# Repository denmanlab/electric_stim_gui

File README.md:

# STG5 and BRAINSBoard GUI
### This will be a quick guide on how to use all the different tools developed for the BRAINSBoard, STG5 and more!

These are both useful tools used in conjunction with one another to easily allow for multi-channel stimulation of the NeuroNexus A1x16 16-Channel Electrode.
# SECTION 1: HARDWARE
## BRAINSBoard:
### Purpose

The BRAINSBoard is a proprietary custom PCB that is designed to electronically switch between Cathode, Anode, Ground, and Floating states for 16 different electrode channels without physically interacting with the components during experiments. This enables:
- Stimulation at different loci in patterns.
- Grounding of every inactive pin to prevent noise.
- Use with a GUI designed for efficient pin switching during and between experiments.

### Components of the Board

#### Connectors
- $\textbf{\color{yellow}Raspberry Pi/Arduino 2x20 Female Header}$ facilitates connections to control and process data from Arduino/Raspberry Pi. $\textbf{\color{yellow}2x20 90º Male Header}$ allows external connections to unused/useful pins
  - Raspberry Pi can be directly connected on top of the $\textbf{\color{yellow}2x20 Female Header}$. Connection Pinout as follows:

  - An Arduino can be connected to those same pins with the following Pinout (demonstrated with Arduino Pro Mini):

  - Other tools (ie. sensors, actuators, external triggers) can be accessed from the $\textbf{\color{yellow}2x20 90º Male Header}$ with the following Pinout:

- $\textbf{\color{white}NeuroNexus}$ Standard 2x8 Box Connectors with grounding on all top pins to minimize noise. Pinout:

- $\textbf{\color{red}Banana Connectors:}$ Connects to cathode and anode pulses from an Isolated Analog Power Stimulator (preferred STG5) and a Signal Ground that can be connected to the same common ground as the electrode and stimulator.

#### Products Used:

$\textbf{\color{yellow}External Connectors:}$

[2x20 Female Header](https://www.digikey.com/en/products/detail/te-connectivity-amp-connectors/2-215307-0/1149668)

[2x20 90º Male Header](https://www.digikey.com/en/products/detail/oupiin/2011-2X20G00RB/13251482)

$\textbf{\color{white}Connectors to Neuronexus:}$

**Samtec Box Header** from [Digikey](https://www.digikey.com/en/products/detail/samtec-inc/TSS-108-01-G-D/2345166):

$\textbf{\color{red}Connectors to Analog Stimulus Isolator:}$

[Ground Connector](https://www.digikey.com/en/products/detail/cliff-electronic-components-ltd/FCR7350G/17729033)

[Cathode Stimulus Connector](https://www.digikey.com/en/products/detail/pomona-electronics/73099-2/10483465)

[Anode Stimulus Connector](https://www.digikey.com/en/products/detail/pomona-electronics/73099-0/10483460)

### Electronics for Selecting Channels:

The following are used to be able to utilize Arduino Logic and rapidly change the connection between our stimulus signal from the isolated stimulator and the respective electrode channels.

#### $\textbf{\color{#FF69B4}Octal Transparent D-Type Latch}$
- Requires a VCC +5V and ground.
- Output Enable and Latch Enable controls, connected to Arduino/Raspberry Pi, to manage pin outputs.
- Utilizes multiplexing capabilities to reduce connections needed to the microcontronoller and allows for future scalability.
- Latch capabilities ensure channel selection stability until change is required.
- [Texas Instruments Octal Transparent D-Type Latch](https://www.digikey.com/en/products/detail/texas-instruments/CY74FCT373TSOC/1508737)

#### $\textbf{\color{orange}Analog SP3T Switch}$
- Two inputs determine the current path (cathode, anode, ground, or floating).
- Output directed through a connector managing pin outputs.
- Useful digital switch to ensure one of the four output states is set at all times.
- [Texas Instruments Analog SP3T Switch](https://www.digikey.com/en/products/detail/texas-instruments/TS5A3357DCUR/695801)

#### $\textbf{\color{cyan}Solid State Relay}$
- Activated by a control switch, it powers an LED internally, which in turn activates a photosensitive diode to close the circuit.
- Optical Isolation prevents electrical interference from the microcontroller side of the circuit to the Analog Isolator stimulus sent to the respective channels.
- These specific Solid State Relays will be useful in handling high variance in Volatge due to unpredictable resistance in the brain as current stimulus is sent.
- [IXYS 600V 100mA Dual Single Pole Normally Open Relay](https://www.digikey.com/en/products/detail/ixys-integrated-circuits-division/PAA193STR/3077694)

#### $\textbf{\color{green}LEDS}$
- Top LED is a $\text{\color{red}RED LED}$ that is utilized to indicate whether or not the BRAINS Board is receiving power.
- Bottom LED is a $\text{\color{green}GREEN LED}$ that is utilized to indicate whether the Output Enable is activated, determining whether or not outputs are being sent to change channels

# SECTION 2: BRAINS BOARD SPECIFIC SOFTWARE

There are various sets of code designed to interface with the BRAINS Board through either the Arduino or Raspberry Pi.
These are guides on how they are designed as well as a simple measure as to how they may be manipulated for various uses.

## PART 1: Using Serial Communication with Arduino to Map Channels:

The current BRAINS Board API is built around Serial Inputs that are translated into pin activation using the [Brainsboard Serial Program Arduino Code](brainsboard_serial_pgm.ino)

This is also all right now designed to be used alongside an Arduino Micro Pro with the pinout shown above in [this image](images/BB2ProMicro_bb.png), though it can easily be changed to work with any Arduino board and pinout using the #define functions.

The following pins correspond to channels above:
| Electrode Channel |    Arduino Pins     |
|:-----------------:|:-------------------:|
| Channel **1**     | Pin 16 + 1 + 5 + 6  |
| Channel **2**     | Pin 16 + 1 + 7 + 8  |
| Channel **3**     | Pin 16 + 1 + 9 + 10 |
| Channel **4**     | Pin 16 + 1 + 14 + 15|
| Channel **5**     | Pin 16 + 2 + 5 + 6  |
| Channel **6**     | Pin 16 + 2 + 7 + 8  |
| Channel **7**     | Pin 16 + 2 + 9 + 10 |
| Channel **8**     | Pin 16 + 2 + 14 + 15|
| Channel **9**     | Pin 16 + 3 + 5 + 6  |
| Channel **10**    | Pin 16 + 3 + 7 + 8  |
| Channel **11**    | Pin 16 + 3 + 9 + 10 |
| Channel **12**    | Pin 16 + 3 + 14 + 15|
| Channel **13**    | Pin 16 + 4 + 5 + 6  |
| Channel **14**    | Pin 16 + 4 + 7 + 8  |
| Channel **15**    | Pin 16 + 4 + 9 + 10 |
| Channel **16**    | Pin 16 + 4 + 14 + 15|

**The logic is this way because of the following:**

- Our **Output Enable** pin, that is connected to all 4 of the Octal Latches, is connected to **Arduino Pin 16**
- We have 4 **Latch Enable** pins that are used to determine which latch we are controlling
  - **Pin 1** is connected to the first **OCTAL LATCH**, which controls signals sent to the **SP3T** switches that set channel configuration for **Electrode Channels 1-4**
  - **Pin 2** is connected to the second **OCTAL LATCH**, which controls signals sent to the **SP3T** switches that set channel configuration for **Electrode Channels 5-8**
  - **Pin 3** is connected to the third **OCTAL LATCH**, which controls signals sent to the **SP3T** switches that set channel configuration for **Electrode Channels 9-12**
  - **Pin 4** is connected to the fourth **OCTAL LATCH**, which controls signals sent to the **SP3T** switches that set channel configuration for **Electrode Channels 13-16**
- We then have **8 Data Input** pins connected to all of the **Octal Latches**, which will change the state of the digital output of the latches to High or Low dependent on a) if the latch enable for said Octal Latch is on and b) if the Arduino pin connected to each digital input pin is high or low
  - **Pins 5 and 6** control the output to the **SP3T** controlling **Electrode Channels 1, 5, 9, and 13**.
  - **Pins 7 and 8** control the output to the **SP3T** controlling **Electrode Channels 2, 6, 10, and 14**.
  - **Pins 9 and 10** control the output to the **SP3T** controlling **Electrode Channels 3, 7, 11, and 15**.
  - **Pins 14 and 15** control the output to the **SP3T** controlling **Electrode Channels 4, 8, 12, and 16**.

**Important Note:** The **A0 pin** is used as an input of any External Triggers from any other device (ie. a stimulator) for the board to use as an input to switch channels, if required.

The code also has 4 states that any channel can be set to at any given moment: **FLOATING**, **CATHODE**, **ANODE**, and **SIGNAL GROUND**. The board is designed to allow the **OCTAL LATCH** to send 2 outputs to any given **SP3T** correlated to a specific electrode channel, and logic of the switch by the **SP3T** is treated as follows:
| INPUT 1 STATE | INPUT 2 STATE | CHANNEL CONNECTED |
|:-------------:|:-------------:|:-----------------:|
| **LOW**       | **LOW**       | **FLOATING**      |
| **HIGH**      | **LOW**       | **CATHODE**       |
| **LOW**       | **HIGH**      | **ANODE**         |
| **HIGH**      | **HIGH**      | **SIGNAL GROUND** |

**Important Note:** The **SIGNAL GROUND** is connecting any signal connected to the $\textbf{\color{green}Green Banana Connector}$, which should ideally connected to the same **Reference Ground** that you would use for any electrophysiology or stimulation experiment.

### Serial Communication Logic:
**The following is a step-by-step guide for utilizing any serial communication to control the channel outputs at any given time**
1. Ensure you are using 115200 bps as the data rate for for Serial line
2. '[' Begins reading channel Data
3. **'{X1}'** is a *Hexadecimal Number*
    - **To Set Channels 1-10:** X1 corresponds to a numerical value Channel # - 1 (ie. Channel 1 is 0, Channel 2 is 1, ..., Channel 10 is 9)
    - **To Set Channels 11-16:** X1 corresponds to an alphabtical value between A-F (ie. Channel 11 is A, Channel 12 is B, ..., Channel 16 is F)
4. **'{X2}'** is a *Character*
      - **F** for **FLOATING**
      - **C** for **CATHODE**
      - **A** for **ANODE**
      - **G** for **SIGNAL GROUND**
5. **']'** Closes *Reading Channel States* and *"Applies"* the channel states by utilizing logic to change where channels are connected
6. **'x'** Sets a *wait* until the **External Trigger Pin** recieves a signal (and won't continue until that trigger is low to change anything)
7. **'{t}{u}'** Sets a *wait* for a set time
      - **'{t}'** is a *numerical value* that is read and stored until the serial code reads a non-numerical value
      - **'{u}'** is a *character* that is written after the numerical values have been written that determines the units of delay time
        - **s** will set the *time {t}* to seconds
        - **m** will set the *time {t}* to milliseconds
        - **u** will set the *time {t}* to microseconds
8. **'l{c}'** Sets up a *loop* for the inputted channel setups for *{c}* more counts
      - If *{c}* is not set, it will infinitely loop.
9. **Important Note:** It is not necessary to write out every channel, previous channel states are already stored and latched until that specific channel is changed
#### Example Serial Command:
**[0F1F2F3F4F5F6F7F8F9FAFBFCFDFEFFF]200u[0C1A]x[0G1GEAFC]2sl3**
- This will first **set every channel** to **FLOATING**
- It will then **wait 200 microseconds**
- It will then change **Channel 1** to **CATHODE** and **Channel 2** to **ANODE**
- It will then **wait** until it recieves the **External Trigger** at **Pin A0**
- It will then change **Channel 1** and **Channel 2** to **SIGNAL GROUND** and **Channel 15** to **ANODE** and **Channel 16** to **CATHODE**
- It will then **wait 2 seconds**
- It then reads **l3**, so it will **loop** the previous steps **3 more times**

## PART 2: Using the Raspberry Pi to Map Channels Directly

The BRAINS Board was initially designed to directly integrate the various connections on a Raspberry Pi to map pins to channels and work harmoniously as a modular device that can work alongside other tools in an experimental setting. There are both benefits and drawbacks to using this microcontroller over an Arduino, laid out as follows:
### BENEFITS:
1. BRAINS Board easily snaps into a Raspberry Pi, no external connection is needed
2. Any pins not used to directly control the logic of the BRAINS Board can be easily accessed through the side male pins, following the pinout shown above in [this image](images/BB_2_external_pins_Pinout.png)
3. Doesn't rely on Serial Communication to switch pinout, which can reduce latency
4. Allows for communication over WiFi which allows for non-wired control to directly switch channels
**When Using This Microcontroller Is Better:** The ideal use for the Raspberry Pi over an Arduino is when you are just reading an external signal or series of them and want to create a closed loop transition between channels based on multiple complicated inputs feeding directly into the Raspberry Pi, given that those inputs are able to be read by the Linux system and processed that way, **OR** when latency isn't very important but non-wired communication is essential or easier. 
### DRAWBACKS:
1. Raspberry Pi uses CPU for running Debian, can create unwanted latency due to other processes running
2. Latency of WiFi communication relatively high
3. Serial read latency of Raspberry Pi is higher than Arduino Serial read latency
4. Debian (Linux) software won't run various softwares (many stimulator softwares are written specifically for Windows computer)
**When Using This Microcontroller is Not Optimal:** The Arduino controller is better when running integrated software with other devices that need a computer to process the information or program other things at the same time (ie. the STG5 Isolated Analog Stimulator, a MultiChannelSystems product that can only be customizably programmed on a Windows using their .dll Package for Windows) **OR** if latency based on external readings is critical and the processing can't be done on a Raspberry Pi (ie. if there were a developed closed-loop system based on the readings of inserted Neuropixels real-time to manipulate activated channels in a closed-loop system).

With that said, there are only a few changes in terms of the pinout when programming as such, all already established with the [GPIO](GPIO.py) script already set. The connections to the BRAINS Board from GPIO pins on the Raspberry Pi are as follows:

| PIN ON BRAINS BOARD | GPIO PIN ON RASPBERRY PI |
|:-------------------:|:------------------------:|
|**OE PIN**           | 22                       |
|**LE PIN 1**         | 23                       |
|**LE PIN 2**         | 24                       |
|**LE PIN 3**         | 25                       |
|**LE PIN 4**         | 27                       |
|**DIGITAL INPUT 1**  | 5                        |
|**DIGITAL INPUT 2**  | 6                        |
|**DIGITAL INPUT 3**  | 12                       |
|**DIGITAL INPUT 4**  | 13                       |
|**DIGITAL INPUT 5**  | 16                       |
|**DIGITAL INPUT 6**  | 17                       |
|**DIGITAL INPUT 7**  | 19                       |
|**DIGITAL INPUT 8**  | 26                       |

The GPIO code uses these and just takes 16 individual strings as channel_state = [...] with **F** for **FLOATING**, **C** for **CATHODE**, **A** for **ANODE**, and **G** for **SIGNAL GROUND** and the delay can be set using the precise_sleep function. Use general Python functionality to be able to program this any which way.

# SECTION 3: STG5

The stimulator of choice for this project is the [Multi Channel Systems STG5](https://www.multichannelsystems.com/products/stg5-base). This product has all the stimulating capabilities that we require for our electrophysiology experiments, can both recieve external triggers and produce a digital output that can be aligned with an analog stimulus sent, and is most importantly programmable beyond the base software that comes with the STG5. We designed our own custom GUI to perform stimulation experiments for monopolar, bipolar, and multipolar stimulation that can be paired with the BRAINS Board. Lets break down the various features of our GUI:

## FEATURE 1: LOCALHOST WEB GUI:

The GUI is all written in Python, but utilizes the [Holoviz Panel Library](https://panel.holoviz.org/index.html) to setup a locally hosted Web GUI that can run on any device
**IMPORTANT NOTE:** THE GUI MUST BE RUN ON A WINDOWS DEVICE IN ORDER TO CONNECT WITH THE STG5 GUI
**IMPORTANT NOTE 2:** THE MCSUsbNet .dll package must be setup from [here](https://github.com/multichannelsystems/McsUsbNet/tree/086642d15fa1b8b805cdc137db4652151c30f9f5) in order to work. Ensure that the packages and files in the MCSUsbNet folder in this repository have all the required permissions to run, otherwise there will be errors.

**Once everything is setup, run the [STG5 and BRAINS Board Joint GUI](STG5_BRAINSBoard_Joint_GUI.py) Python Script to start up the GUI so that you can manipulate the next features

## FEATURE 2: EVENT SETTINGS:

When you first run the GUI, the *EVENT SETTINGS* tab will be the primary tab opened. You will notice the following:
- First you will have the *Waveform Type Selector* that has three options: **Monophasic**, **Biphasic**, and **Sinusoidal**
- You will have the *Modulation Type Selector* directly underneath it, giving the options of sending a set **Voltage** or **Current** from the STG5
- You then have the *Amplitude Selection* underneath those two Radio Buttons
  - On the left is the *Amplitude Slider* where you can easily set the numeric value for your Amplitude
  - Next to the slider, you get the *Unit Selector*, which gives you the option of setting the units of your waveform. If **Voltage** is selected from your *Modulation Type Selector*, your options are **uV**, **mV** or **V** and if **Current** is selected from your *Modulation Type Selector*, your options are **uA**, **mA**, or **A**.
  - You also have the *Randomize* slider and button, which allows you to choose a range and randomize the amplitude of your waveform when the random button is clicked.
- If **Monophasic** or **Biphasic** is selected:
  - There is a *Pulse Duration Slider* and *Unit Selector Button* for setting the Pulse Duration in microseconds, milliseconds, or seconds
  - If **Biphasic** specifically is selected, there will be text stating whether the waveform is **Cathode Leading**, **Anode Leading**, or **Neither** and it is **IMPORTANT TO NOTE: THE PULSE DURATION IS SET FOR ONE HALF OF THE WAVEFORM, NOT TOTAL PUSLE DURATION**
  - You also get a *Randomizer* pulse duration if needed.
- If **Sinusoidal** is selected:
   - You get a *Wavelength Type Selector* that gives you the option to choose between setting the Period or Frequency of the Waveform, with a *Wavelength Slider* with the same functionality as other sliders with a *Unit Selector* and *Randomizer*
   - There will also be a conversion printed at the bottom with either Frequency or Period, opposite of what is selected in the selector
- There is also a *Number of Events* input, normally set to 1.
   - If set to one, nothing else needs to be done
   - If set >1, there will be an option to set a duration between events using the *duration between events slider* with both *unit selection* and *randomize* functionality.
This is all the settings for one "event", giving basic functionality for setting up a waveform.

## FEATURE 2: TRAIN SETTINGS
This feature is established to allow you to repeat events as individual trains for however many trains are needed for an experiment. The following can be set:
- First and foremost is the *External Trigger checkbox* that allows you to start a train based on an external trigger recieved by the STG5. Functionality of this function is still in the process of being built.
- Next is the *Number of Trains Input* that allows you to set the number of trains in one run
- If more than 1 train in set, you can then use the *Time Between Trains* slider to set the amount of **time between the start of one train to the start of the next train** (ensure this is bigger than the total time of one event) that also has *unit selection* and *randomize* features.

## FEATURE 3: EXTERNAL SIGNAL SETTINGS
This feature allows you to send out an external digital signal from a channel of the STG5 of any specified length at the beginning of every train. This is done using the *External Signal Slider* with *unit selection* and *randomize* functionality.
## $\textbf{\color{white}This work was supported by NIH NINDS project number 1R01NS120850}$

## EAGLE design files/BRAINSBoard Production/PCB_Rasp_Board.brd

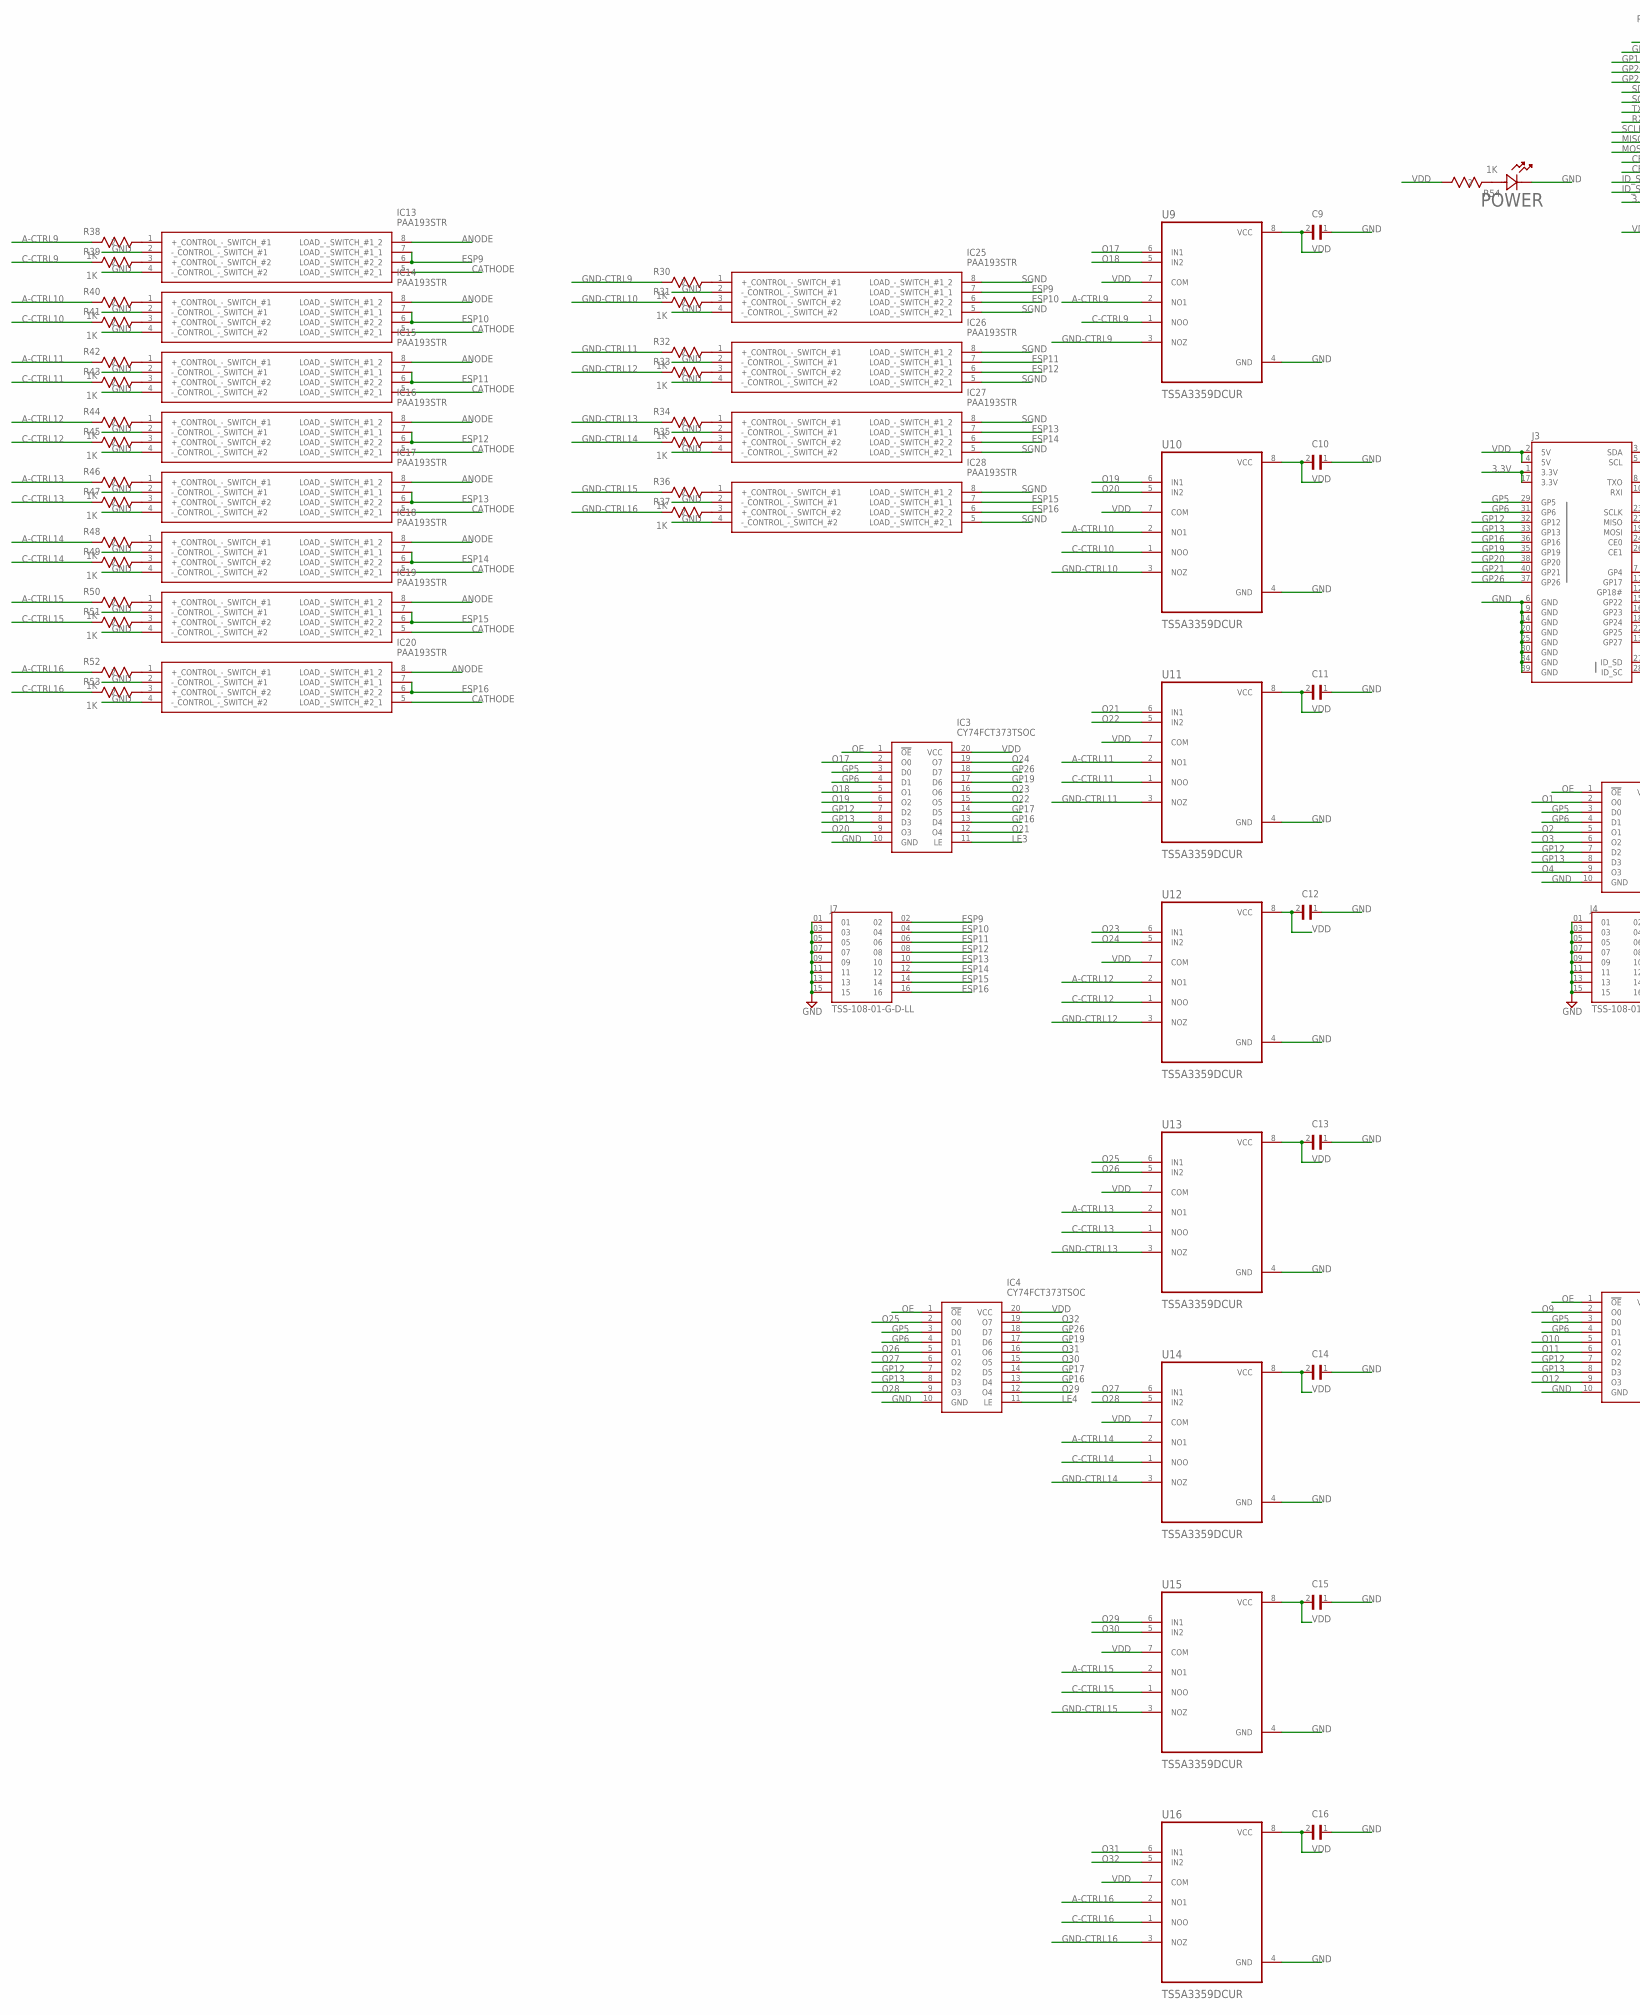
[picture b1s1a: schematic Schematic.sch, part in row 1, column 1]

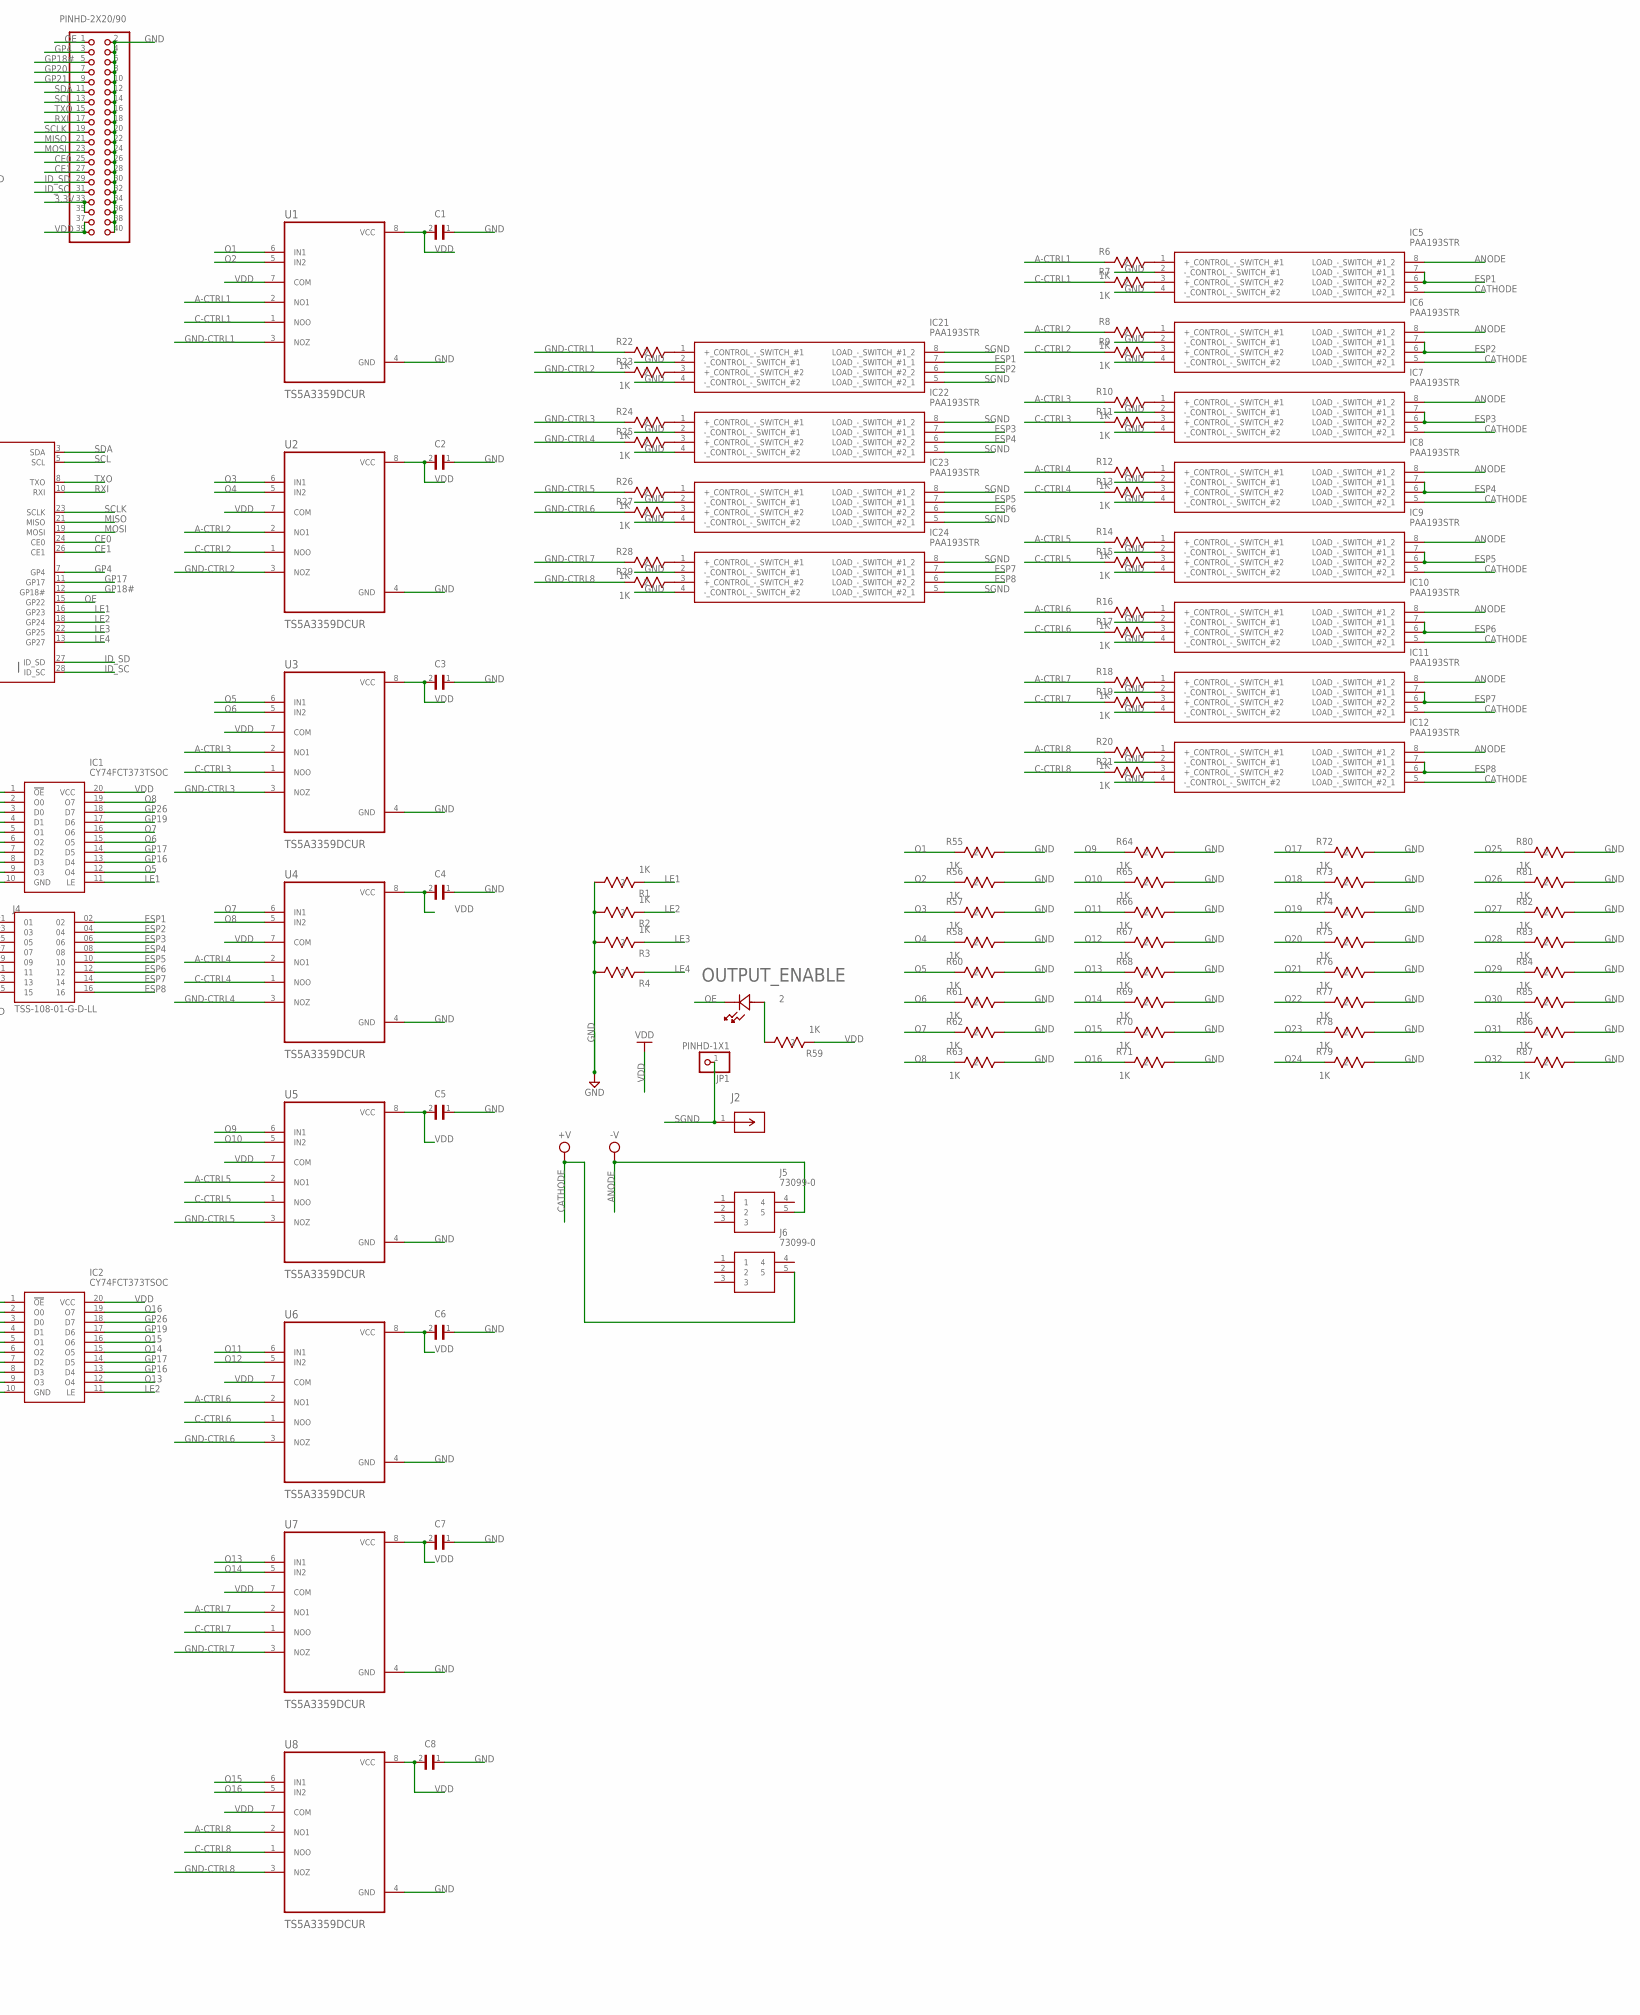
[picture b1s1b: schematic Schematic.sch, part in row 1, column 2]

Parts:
C1, C2, C3, C4, C5, C6, C7, C8, C9, C10, C11, C12, C13, C14, C15, C16: CL05A104KA5NNNC; CAPC1005X55N
IC1, IC2, IC3, IC4: CY74FCT373TSOC; SOIC127P1030X265-20N
IC5, IC6, IC7, IC8, IC9, IC10, IC11, IC12, IC13, IC14, IC15, IC16, IC17, IC18, IC19, IC20, IC21, IC22, IC23, IC24, IC25, IC26, IC27, IC28: PAA193STR; SOP254P952X457-8N
J2: FCR7350GCONN_FCR7350G_CLF; CONN_FCR7350G_CLF
J3: RASPBERRYPI-40-PIN-GPIO_PTH_NO_SHROUD; 2X20
J4, J7: TSS-108-01-G-D-LL; SAMTEC_TSS-108-01-G-D-LL
J5, J6: 73099-0; 730990
JP1: PINHD-1X1; 1X01
JP4: PINHD-2X20/90; 2X20/90
OUTPUT_ENABLE: LTST-C190GKTLED_LTST-C190CKT_LTO; LED_LTST-C190CKT_LTO
POWER: LTST-C190GKTLED_LTST-C190CKT_LTO; LED_LTST-C190CKT_LTO
R1, R2, R3, R6, R7, R8, R9, R10, R11, R12, R13, R14, R15, R16, R17, R18, R19, R20, R21, R22, R23, R24, R25, R26, R27, R28, R29, R30, R31, R32, R33, R34, R35, R36, R37, R38, R39, R40, R41, R42, R43, R44, R45, R46, R47, R48, R49, R50, R51, R52, R53, R54, R55, R56, R57, R58, R59, R60, R61, R62, R63, R64, R65, R66, R67, R68, R69, R70, R71, R72, R73, R74, R75, R76, R77, R78, R79, R80, R81, R82, R83, R84, R85, R86, R87: 1K; RC0402N_YAG
R4: RC0402JR-071KLRC0402N_YAG; RC0402N_YAG
U1, U2, U3, U4, U5, U6, U7, U8, U9, U10, U11, U12, U13, U14, U15, U16: TS5A3359DCUR; SOP50P310X90-8N

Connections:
2: OUTPUT_ENABLE.2, R59.1
3.3V: J3.1 (3.3V), J3.17 (3.3V), JP4.33, JP4.35
A-CTRL1: R6.2, U1.2 (NO1)
A-CTRL2: R8.2, U2.2 (NO1)
A-CTRL3: R10.2, U3.2 (NO1)
A-CTRL4: R12.2, U4.2 (NO1)
A-CTRL5: R14.2, U5.2 (NO1)
A-CTRL6: R16.2, U6.2 (NO1)
A-CTRL7: R18.2, U7.2 (NO1)
A-CTRL8: R20.2, U8.2 (NO1)
A-CTRL9: R38.2, U9.2 (NO1)
A-CTRL10: R40.2, U10.2 (NO1)
A-CTRL11: R42.2, U11.2 (NO1)
A-CTRL12: R44.2, U12.2 (NO1)
A-CTRL13: R46.2, U13.2 (NO1)
A-CTRL14: R48.2, U14.2 (NO1)
A-CTRL15: R50.2, U15.2 (NO1)
A-CTRL16: R52.2, U16.2 (NO1)
ANODE: IC5.8 (LOAD_-_SWITCH_#1_2), IC6.8 (LOAD_-_SWITCH_#1_2), IC7.8 (LOAD_-_SWITCH_#1_2), IC8.8 (LOAD_-_SWITCH_#1_2), IC9.8 (LOAD_-_SWITCH_#1_2), IC10.8 (LOAD_-_SWITCH_#1_2), IC11.8 (LOAD_-_SWITCH_#1_2), IC12.8 (LOAD_-_SWITCH_#1_2), IC13.8 (LOAD_-_SWITCH_#1_2), IC14.8 (LOAD_-_SWITCH_#1_2), IC15.8 (LOAD_-_SWITCH_#1_2), IC16.8 (LOAD_-_SWITCH_#1_2), IC17.8 (LOAD_-_SWITCH_#1_2), IC18.8 (LOAD_-_SWITCH_#1_2), IC19.8 (LOAD_-_SWITCH_#1_2), IC20.8 (LOAD_-_SWITCH_#1_2), J5.5
C-CTRL1: R7.2, U1.1 (NOO)
C-CTRL2: R9.2, U2.1 (NOO)
C-CTRL3: R11.2, U3.1 (NOO)
C-CTRL4: R13.2, U4.1 (NOO)
C-CTRL5: R15.2, U5.1 (NOO)
C-CTRL6: R17.2, U6.1 (NOO)
C-CTRL7: R19.2, U7.1 (NOO)
C-CTRL8: R21.2, U8.1 (NOO)
C-CTRL9: R39.2, U9.1 (NOO)
C-CTRL10: R41.2, U10.1 (NOO)
C-CTRL11: R43.2, U11.1 (NOO)
C-CTRL12: R45.2, U12.1 (NOO)
C-CTRL13: R47.2, U13.1 (NOO)
C-CTRL14: R49.2, U14.1 (NOO)
C-CTRL15: R51.2, U15.1 (NOO)
C-CTRL16: R53.2, U16.1 (NOO)
CATHODE: IC5.5 (LOAD_-_SWITCH_#2_1), IC6.5 (LOAD_-_SWITCH_#2_1), IC7.5 (LOAD_-_SWITCH_#2_1), IC8.5 (LOAD_-_SWITCH_#2_1), IC9.5 (LOAD_-_SWITCH_#2_1), IC10.5 (LOAD_-_SWITCH_#2_1), IC11.5 (LOAD_-_SWITCH_#2_1), IC12.5 (LOAD_-_SWITCH_#2_1), IC13.5 (LOAD_-_SWITCH_#2_1), IC14.5 (LOAD_-_SWITCH_#2_1), IC15.5 (LOAD_-_SWITCH_#2_1), IC16.5 (LOAD_-_SWITCH_#2_1), IC17.5 (LOAD_-_SWITCH_#2_1), IC18.5 (LOAD_-_SWITCH_#2_1), IC19.5 (LOAD_-_SWITCH_#2_1), IC20.5 (LOAD_-_SWITCH_#2_1), J6.5
CE0: J3.24 (CE0), JP4.25
CE1: J3.26 (CE1), JP4.27
ESP1: IC5.6 (LOAD_-_SWITCH_#2_2), IC5.7 (LOAD_-_SWITCH_#1_1), IC21.7 (LOAD_-_SWITCH_#1_1), J4.02
ESP2: IC6.6 (LOAD_-_SWITCH_#2_2), IC6.7 (LOAD_-_SWITCH_#1_1), IC21.6 (LOAD_-_SWITCH_#2_2), J4.04
ESP3: IC7.6 (LOAD_-_SWITCH_#2_2), IC7.7 (LOAD_-_SWITCH_#1_1), IC22.7 (LOAD_-_SWITCH_#1_1), J4.06
ESP4: IC8.6 (LOAD_-_SWITCH_#2_2), IC8.7 (LOAD_-_SWITCH_#1_1), IC22.6 (LOAD_-_SWITCH_#2_2), J4.08
ESP5: IC9.6 (LOAD_-_SWITCH_#2_2), IC9.7 (LOAD_-_SWITCH_#1_1), IC23.7 (LOAD_-_SWITCH_#1_1), J4.10
ESP6: IC10.6 (LOAD_-_SWITCH_#2_2), IC10.7 (LOAD_-_SWITCH_#1_1), IC23.6 (LOAD_-_SWITCH_#2_2), J4.12
ESP7: IC11.6 (LOAD_-_SWITCH_#2_2), IC11.7 (LOAD_-_SWITCH_#1_1), IC24.7 (LOAD_-_SWITCH_#1_1), J4.14
ESP8: IC12.6 (LOAD_-_SWITCH_#2_2), IC12.7 (LOAD_-_SWITCH_#1_1), IC24.6 (LOAD_-_SWITCH_#2_2), J4.16
ESP9: IC13.6 (LOAD_-_SWITCH_#2_2), IC13.7 (LOAD_-_SWITCH_#1_1), IC25.7 (LOAD_-_SWITCH_#1_1), J7.02
ESP10: IC14.6 (LOAD_-_SWITCH_#2_2), IC14.7 (LOAD_-_SWITCH_#1_1), IC25.6 (LOAD_-_SWITCH_#2_2), J7.04
ESP11: IC15.6 (LOAD_-_SWITCH_#2_2), IC15.7 (LOAD_-_SWITCH_#1_1), IC26.7 (LOAD_-_SWITCH_#1_1), J7.06
ESP12: IC16.6 (LOAD_-_SWITCH_#2_2), IC16.7 (LOAD_-_SWITCH_#1_1), IC26.6 (LOAD_-_SWITCH_#2_2), J7.08
ESP13: IC17.6 (LOAD_-_SWITCH_#2_2), IC17.7 (LOAD_-_SWITCH_#1_1), IC27.7 (LOAD_-_SWITCH_#1_1), J7.10
ESP14: IC18.6 (LOAD_-_SWITCH_#2_2), IC18.7 (LOAD_-_SWITCH_#1_1), IC27.6 (LOAD_-_SWITCH_#2_2), J7.12
ESP15: IC19.6 (LOAD_-_SWITCH_#2_2), IC19.7 (LOAD_-_SWITCH_#1_1), IC28.7 (LOAD_-_SWITCH_#1_1), J7.14
ESP16: IC20.6 (LOAD_-_SWITCH_#2_2), IC20.7 (LOAD_-_SWITCH_#1_1), IC28.6 (LOAD_-_SWITCH_#2_2), J7.16
GND: C1.1, C2.1, C3.1, C4.1, C5.1, C6.1, C7.1, C8.1, C9.1, C10.1, C11.1, C12.1, C13.1, C14.1, C15.1, C16.1, IC1.10 (GND), IC2.10 (GND), IC3.10 (GND), IC4.10 (GND), IC5.2 (-_CONTROL_-_SWITCH_#1), IC5.4 (-_CONTROL_-_SWITCH_#2), IC6.2 (-_CONTROL_-_SWITCH_#1), IC6.4 (-_CONTROL_-_SWITCH_#2), IC7.2 (-_CONTROL_-_SWITCH_#1), IC7.4 (-_CONTROL_-_SWITCH_#2), IC8.2 (-_CONTROL_-_SWITCH_#1), IC8.4 (-_CONTROL_-_SWITCH_#2), IC9.2 (-_CONTROL_-_SWITCH_#1), IC9.4 (-_CONTROL_-_SWITCH_#2), IC10.2 (-_CONTROL_-_SWITCH_#1), IC10.4 (-_CONTROL_-_SWITCH_#2), IC11.2 (-_CONTROL_-_SWITCH_#1), IC11.4 (-_CONTROL_-_SWITCH_#2), IC12.2 (-_CONTROL_-_SWITCH_#1), IC12.4 (-_CONTROL_-_SWITCH_#2), IC13.2 (-_CONTROL_-_SWITCH_#1), IC13.4 (-_CONTROL_-_SWITCH_#2), IC14.2 (-_CONTROL_-_SWITCH_#1), IC14.4 (-_CONTROL_-_SWITCH_#2), IC15.2 (-_CONTROL_-_SWITCH_#1), IC15.4 (-_CONTROL_-_SWITCH_#2), IC16.2 (-_CONTROL_-_SWITCH_#1), IC16.4 (-_CONTROL_-_SWITCH_#2), IC17.2 (-_CONTROL_-_SWITCH_#1), IC17.4 (-_CONTROL_-_SWITCH_#2), IC18.2 (-_CONTROL_-_SWITCH_#1), IC18.4 (-_CONTROL_-_SWITCH_#2), IC19.2 (-_CONTROL_-_SWITCH_#1), IC19.4 (-_CONTROL_-_SWITCH_#2), IC20.2 (-_CONTROL_-_SWITCH_#1), IC20.4 (-_CONTROL_-_SWITCH_#2), IC21.2 (-_CONTROL_-_SWITCH_#1), IC21.4 (-_CONTROL_-_SWITCH_#2), IC22.2 (-_CONTROL_-_SWITCH_#1), IC22.4 (-_CONTROL_-_SWITCH_#2), IC23.2 (-_CONTROL_-_SWITCH_#1), IC23.4 (-_CONTROL_-_SWITCH_#2), IC24.2 (-_CONTROL_-_SWITCH_#1), IC24.4 (-_CONTROL_-_SWITCH_#2), IC25.2 (-_CONTROL_-_SWITCH_#1), IC25.4 (-_CONTROL_-_SWITCH_#2), IC26.2 (-_CONTROL_-_SWITCH_#1), IC26.4 (-_CONTROL_-_SWITCH_#2), IC27.2 (-_CONTROL_-_SWITCH_#1), IC27.4 (-_CONTROL_-_SWITCH_#2), IC28.2 (-_CONTROL_-_SWITCH_#1), IC28.4 (-_CONTROL_-_SWITCH_#2), J3.6 (GND), J3.9 (GND), J3.14 (GND), J3.20 (GND), J3.25 (GND), J3.30 (GND), J3.34 (GND), J3.39 (GND), J4.01, J4.03, J4.05, J4.07, J4.09, J4.11, J4.13, J4.15, J7.01, J7.03, J7.05, J7.07, J7.09, J7.11, J7.13, J7.15, JP4.2, JP4.4, JP4.6, JP4.8, JP4.10, JP4.12, JP4.14, JP4.16, JP4.18, JP4.20, JP4.22, JP4.24, JP4.26, JP4.28, JP4.30, JP4.32, JP4.34, JP4.36, JP4.38, JP4.40, POWER.1, R1.1, R2.1, R3.1, R4.1, R55.1, R56.1, R57.1, R58.1, R60.1, R61.1, R62.1, R63.1, R64.1, R65.1, R66.1, R67.1, R68.1, R69.1, R70.1, R71.1, R72.1, R73.1, R74.1, R75.1, R76.1, R77.1, R78.1, R79.1, R80.1, R81.1, R82.1, R83.1, R84.1, R85.1, R86.1, R87.1, U1.4 (GND), U2.4 (GND), U3.4 (GND), U4.4 (GND), U5.4 (GND), U6.4 (GND), U7.4 (GND), U8.4 (GND), U9.4 (GND), U10.4 (GND), U11.4 (GND), U12.4 (GND), U13.4 (GND), U14.4 (GND), U15.4 (GND), U16.4 (GND)
GND-CTRL1: R22.2, U1.3 (NOZ)
GND-CTRL2: R23.2, U2.3 (NOZ)
GND-CTRL3: R24.2, U3.3 (NOZ)
GND-CTRL4: R25.2, U4.3 (NOZ)
GND-CTRL5: R26.2, U5.3 (NOZ)
GND-CTRL6: R27.2, U6.3 (NOZ)
GND-CTRL7: R28.2, U7.3 (NOZ)
GND-CTRL8: R29.2, U8.3 (NOZ)
GND-CTRL9: R30.2, U9.3 (NOZ)
GND-CTRL10: R31.2, U10.3 (NOZ)
GND-CTRL11: R32.2, U11.3 (NOZ)
GND-CTRL12: R33.2, U12.3 (NOZ)
GND-CTRL13: R34.2, U13.3 (NOZ)
GND-CTRL14: R35.2, U14.3 (NOZ)
GND-CTRL15: R36.2, U15.3 (NOZ)
GND-CTRL16: R37.2, U16.3 (NOZ)
GP4: J3.7 (GP4), JP4.3
GP5: IC1.3 (D0), IC2.3 (D0), IC3.3 (D0), IC4.3 (D0), J3.29 (GP5)
GP6: IC1.4 (D1), IC2.4 (D1), IC3.4 (D1), IC4.4 (D1), J3.31 (GP6)
GP12: IC1.7 (D2), IC2.7 (D2), IC3.7 (D2), IC4.7 (D2), J3.32 (GP12)
GP13: IC1.8 (D3), IC2.8 (D3), IC3.8 (D3), IC4.8 (D3), J3.33 (GP13)
GP16: IC1.13 (D4), IC2.13 (D4), IC3.13 (D4), IC4.13 (D4), J3.36 (GP16)
GP17: IC1.14 (D5), IC2.14 (D5), IC3.14 (D5), IC4.14 (D5), J3.11 (GP17)
GP18#: J3.12 (GP18#), JP4.5
GP19: IC1.17 (D6), IC2.17 (D6), IC3.17 (D6), IC4.17 (D6), J3.35 (GP19)
GP20: J3.38 (GP20), JP4.7
GP21: J3.40 (GP21), JP4.9
GP26: IC1.18 (D7), IC2.18 (D7), IC3.18 (D7), IC4.18 (D7), J3.37 (GP26)
ID_SC: J3.28 (ID_SC), JP4.31
ID_SD: J3.27 (ID_SD), JP4.29
LE1: IC1.11 (LE), J3.16 (GP23), R1.2
LE2: IC2.11 (LE), J3.18 (GP24), R2.2
LE3: IC3.11 (LE), J3.22 (GP25), R3.2
LE4: IC4.11 (LE), J3.13 (GP27), R4.2
MISO: J3.21 (MISO), JP4.21
MOSI: J3.19 (MOSI), JP4.23
unnamed: POWER.2, R54.2
unnamed: IC5.1 (+_CONTROL_-_SWITCH_#1), R6.1
unnamed: IC5.3 (+_CONTROL_-_SWITCH_#2), R7.1
unnamed: IC6.1 (+_CONTROL_-_SWITCH_#1), R8.1
unnamed: IC6.3 (+_CONTROL_-_SWITCH_#2), R9.1
unnamed: IC7.1 (+_CONTROL_-_SWITCH_#1), R10.1
unnamed: IC7.3 (+_CONTROL_-_SWITCH_#2), R11.1
unnamed: IC8.1 (+_CONTROL_-_SWITCH_#1), R12.1
unnamed: IC8.3 (+_CONTROL_-_SWITCH_#2), R13.1
unnamed: IC9.1 (+_CONTROL_-_SWITCH_#1), R14.1
unnamed: IC9.3 (+_CONTROL_-_SWITCH_#2), R15.1
unnamed: IC10.1 (+_CONTROL_-_SWITCH_#1), R16.1
unnamed: IC10.3 (+_CONTROL_-_SWITCH_#2), R17.1
unnamed: IC11.1 (+_CONTROL_-_SWITCH_#1), R18.1
unnamed: IC11.3 (+_CONTROL_-_SWITCH_#2), R19.1
unnamed: IC12.1 (+_CONTROL_-_SWITCH_#1), R20.1
unnamed: IC12.3 (+_CONTROL_-_SWITCH_#2), R21.1
unnamed: IC21.1 (+_CONTROL_-_SWITCH_#1), R22.1
unnamed: IC21.3 (+_CONTROL_-_SWITCH_#2), R23.1
unnamed: IC22.1 (+_CONTROL_-_SWITCH_#1), R24.1
unnamed: IC22.3 (+_CONTROL_-_SWITCH_#2), R25.1
unnamed: IC23.1 (+_CONTROL_-_SWITCH_#1), R26.1
unnamed: IC23.3 (+_CONTROL_-_SWITCH_#2), R27.1
unnamed: IC24.1 (+_CONTROL_-_SWITCH_#1), R28.1
unnamed: IC24.3 (+_CONTROL_-_SWITCH_#2), R29.1
unnamed: IC25.1 (+_CONTROL_-_SWITCH_#1), R30.1
unnamed: IC25.3 (+_CONTROL_-_SWITCH_#2), R31.1
unnamed: IC26.1 (+_CONTROL_-_SWITCH_#1), R32.1
unnamed: IC26.3 (+_CONTROL_-_SWITCH_#2), R33.1
unnamed: IC27.1 (+_CONTROL_-_SWITCH_#1), R34.1
unnamed: IC27.3 (+_CONTROL_-_SWITCH_#2), R35.1
unnamed: IC28.1 (+_CONTROL_-_SWITCH_#1), R36.1
unnamed: IC28.3 (+_CONTROL_-_SWITCH_#2), R37.1
unnamed: IC13.1 (+_CONTROL_-_SWITCH_#1), R38.1
unnamed: IC13.3 (+_CONTROL_-_SWITCH_#2), R39.1
unnamed: IC14.1 (+_CONTROL_-_SWITCH_#1), R40.1
unnamed: IC14.3 (+_CONTROL_-_SWITCH_#2), R41.1
unnamed: IC15.1 (+_CONTROL_-_SWITCH_#1), R42.1
unnamed: IC15.3 (+_CONTROL_-_SWITCH_#2), R43.1
unnamed: IC16.1 (+_CONTROL_-_SWITCH_#1), R44.1
unnamed: IC16.3 (+_CONTROL_-_SWITCH_#2), R45.1
unnamed: IC17.1 (+_CONTROL_-_SWITCH_#1), R46.1
unnamed: IC17.3 (+_CONTROL_-_SWITCH_#2), R47.1
unnamed: IC18.1 (+_CONTROL_-_SWITCH_#1), R48.1
unnamed: IC18.3 (+_CONTROL_-_SWITCH_#2), R49.1
unnamed: IC19.1 (+_CONTROL_-_SWITCH_#1), R50.1
unnamed: IC19.3 (+_CONTROL_-_SWITCH_#2), R51.1
unnamed: IC20.1 (+_CONTROL_-_SWITCH_#1), R52.1
unnamed: IC20.3 (+_CONTROL_-_SWITCH_#2), R53.1
O1: IC1.2 (O0), R55.2, U1.6 (IN1)
O2: IC1.5 (O1), R56.2, U1.5 (IN2)
O3: IC1.6 (O2), R57.2, U2.6 (IN1)
O4: IC1.9 (O3), R58.2, U2.5 (IN2)
O5: IC1.12 (O4), R60.2, U3.6 (IN1)
O6: IC1.15 (O5), R61.2, U3.5 (IN2)
O7: IC1.16 (O6), R62.2, U4.6 (IN1)
O8: IC1.19 (O7), R63.2, U4.5 (IN2)
O9: IC2.2 (O0), R64.2, U5.6 (IN1)
O10: IC2.5 (O1), R65.2, U5.5 (IN2)
O11: IC2.6 (O2), R66.2, U6.6 (IN1)
O12: IC2.9 (O3), R67.2, U6.5 (IN2)
O13: IC2.12 (O4), R68.2, U7.6 (IN1)
O14: IC2.15 (O5), R69.2, U7.5 (IN2)
O15: IC2.16 (O6), R70.2, U8.6 (IN1)
O16: IC2.19 (O7), R71.2, U8.5 (IN2)
O17: IC3.2 (O0), R72.2, U9.6 (IN1)
O18: IC3.5 (O1), R73.2, U9.5 (IN2)
O19: IC3.6 (O2), R74.2, U10.6 (IN1)
O20: IC3.9 (O3), R75.2, U10.5 (IN2)
O21: IC3.12 (O4), R76.2, U11.6 (IN1)
O22: IC3.15 (O5), R77.2, U11.5 (IN2)
O23: IC3.16 (O6), R78.2, U12.6 (IN1)
O24: IC3.19 (O7), R79.2, U12.5 (IN2)
O25: IC4.2 (O0), R80.2, U13.6 (IN1)
O26: IC4.5 (O1), R81.2, U13.5 (IN2)
O27: IC4.6 (O2), R82.2, U14.6 (IN1)
O28: IC4.9 (O3), R83.2, U14.5 (IN2)
O29: IC4.12 (O4), R84.2, U15.6 (IN1)
O30: IC4.15 (O5), R85.2, U15.5 (IN2)
O31: IC4.16 (O6), R86.2, U16.6 (IN1)
O32: IC4.19 (O7), R87.2, U16.5 (IN2)
OE: IC1.1 (!OE), IC2.1 (!OE), IC3.1 (!OE), IC4.1 (!OE), J3.15 (GP22), JP4.1, OUTPUT_ENABLE.1
RXI: J3.10 (RXI), JP4.17
SCL: J3.5 (SCL), JP4.13
SCLK: J3.23 (SCLK), JP4.19
SDA: J3.3 (SDA), JP4.11
SGND: IC21.5 (LOAD_-_SWITCH_#2_1), IC21.8 (LOAD_-_SWITCH_#1_2), IC22.5 (LOAD_-_SWITCH_#2_1), IC22.8 (LOAD_-_SWITCH_#1_2), IC23.5 (LOAD_-_SWITCH_#2_1), IC23.8 (LOAD_-_SWITCH_#1_2), IC24.5 (LOAD_-_SWITCH_#2_1), IC24.8 (LOAD_-_SWITCH_#1_2), IC25.5 (LOAD_-_SWITCH_#2_1), IC25.8 (LOAD_-_SWITCH_#1_2), IC26.5 (LOAD_-_SWITCH_#2_1), IC26.8 (LOAD_-_SWITCH_#1_2), IC27.5 (LOAD_-_SWITCH_#2_1), IC27.8 (LOAD_-_SWITCH_#1_2), IC28.5 (LOAD_-_SWITCH_#2_1), IC28.8 (LOAD_-_SWITCH_#1_2), J2.1, JP1.1
TXO: J3.8 (TXO), JP4.15
VDD: C1.2, C2.2, C3.2, C4.2, C5.2, C6.2, C7.2, C8.2, C9.2, C10.2, C11.2, C12.2, C13.2, C14.2, C15.2, C16.2, IC1.20 (VCC), IC2.20 (VCC), IC3.20 (VCC), IC4.20 (VCC), J3.2 (5V), J3.4 (5V), JP4.37, JP4.39, R54.1, R59.2, U1.7 (COM), U1.8 (VCC), U2.7 (COM), U2.8 (VCC), U3.7 (COM), U3.8 (VCC), U4.7 (COM), U4.8 (VCC), U5.7 (COM), U5.8 (VCC), U6.7 (COM), U6.8 (VCC), U7.7 (COM), U7.8 (VCC), U8.7 (COM), U8.8 (VCC), U9.7 (COM), U9.8 (VCC), U10.7 (COM), U10.8 (VCC), U11.7 (COM), U11.8 (VCC), U12.7 (COM), U12.8 (VCC), U13.7 (COM), U13.8 (VCC), U14.7 (COM), U14.8 (VCC), U15.7 (COM), U15.8 (VCC), U16.7 (COM), U16.8 (VCC)

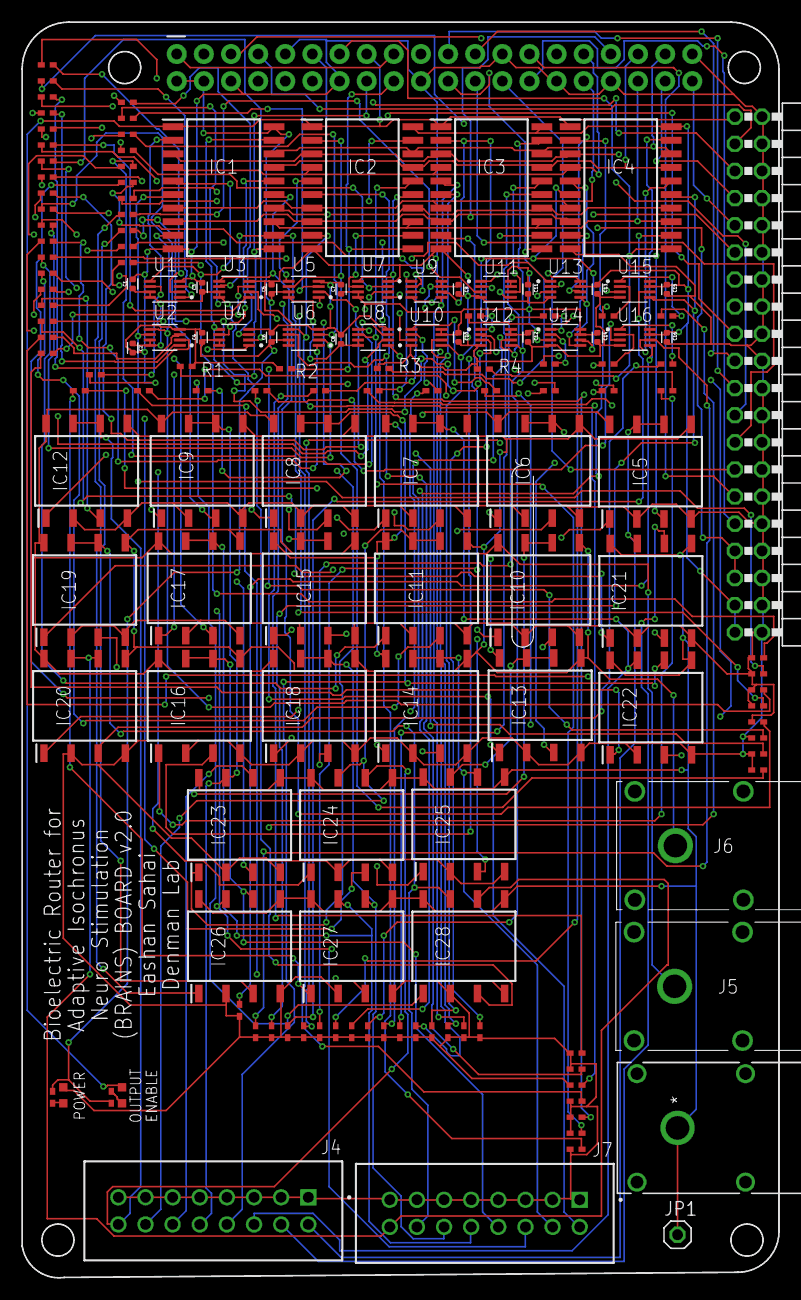
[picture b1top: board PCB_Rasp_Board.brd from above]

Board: 4 copper layers, 70.8 x 117.5 mm, 156 parts (1 on the bottom side), 180 nets.

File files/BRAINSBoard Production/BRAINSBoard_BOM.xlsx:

Comment | Designator | Footprint
1K | R1, R2, R3, R4, R6, R7, R8, R9, R10, R11, R12, R13, R14, R15, R16, R17, R18, R1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 | RC0402JR-071KL
73099-0 | J5 | 730990
73099-2 | J6 | 730990
CL05A104KA5NNNC | C1, C2, C3, C4, C5, C6, C7, C8, C9, C10, C11, C12, C13, C14, C15, C16 | CAPC1005X55N
PAA193STR | IC5, IC6, IC7, IC8, IC9, IC10, IC11, IC12, IC13, IC14, IC15, IC16, IC17, IC18, 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 | SOP254P952X457-8N
PINHD-1X1 | JP1 | 1X01
2-215307-0 | J3 | 2X20
CY74FCT373TSOC | IC1, IC2, IC3, IC4 | SOIC127P1030X265-20N
TS5A3357DCUR | U1, U2, U3, U4, U5, U6, U7, U8, U9, U10, U11, U12, U13, U14, U15, U16 | SOP50P310X90-8N
TSS-108-01-G-D-LL | J4, J7 | SAMTEC_TSS-108-01-G-D-LL
4654-FCR7350G-ND | J2 | CONN_FCR7350G_CLF
LTST-C191KGKT | OUTPUT ENABLE | 0603 SMD/LED_LTST-C190CKT_LTO
LTST-C191KRKT | POWER | 0603 SMD/LED_LTST-C190CKT_LTO
2011-2X20G00RB | JP4 | 2X20/90

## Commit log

2024-04-17 Added the initial files that I believe are functional for STG5 and Brainsboard. Try.c is for arduino, rest_api.py is for raspberry pi. Newest and best stimulator gui is STG5_Gui_With_Channels_Extende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
2024-04-18 added some images and files that are related to the board
2024-04-18 added some more images and files to help with documentation
2024-04-18 changed name of labelled image
2024-04-18 Added a few more images
2024-04-22 Update README.md
    try
2024-04-22 trying to restart pics
2024-04-22 added pics
2024-04-22 changed image names
2024-05-13 Added the arduino code to control the brainsboard
2024-05-13 Finished up the hardware side of the readme
2024-05-13 Added Arduino Control Section
2024-05-13 Rename stg5_gui_with_channels_extended.py to STG5_BRAINSBoard_Joint_GUI.py
2024-07-11 best setup 7/11/2024
    fixed issues based on readings

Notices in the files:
parts and their libraries:
SparkFun-Connectors-Local: Licensing: Creative Commons ShareAlike 4.0 International - https://creativecommons.org/licenses/by-sa/4.0
COPYRIGHT: Copyright (C) 2023 Ultra Librarian. All rights reserved.
COPYRIGHT: Copyright (C) 2024 Ultra Librarian. All rights reserved.
